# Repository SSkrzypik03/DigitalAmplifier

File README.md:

<p align="center">
  <picture>
    <source media="(prefers-color-scheme: dark)" srcset="img/volumia_logo_dark.png">
    <source media="(prefers-color-scheme: light)" srcset="img/volumia_logo_white.png">
    
  </picture>
</p>

<p align="center">
  High-performance Class-D audio amplifier with integrated DSP and PFFB
</p>

---

## Overview

Volumia is a high-performance stereo Class-D amplifier project based on the TPA3255 platform with Post-Filter Feedback (PFFB) and a dedicated STM32F446 DSP subsystem.

The goal is to deliver a compact and fully integrated 2×75 W amplifier combining digital signal processing, high audio quality and efficient power conversion.

## Main Features

## Audio & Electronics

- Class-D topology based on TPA3255
- Post-Filter Feedback (PFFB) architecture
- DSP processing using STM32F446
- 2×75 W RMS output power
- THD+N: TBD after laboratory measurements
- IMD: TBD after laboratory measurements

## Connectivity & User Interface

- USB Type-C input
- S/PDIF input
- RCA line input
- PREOUT output
- 3.83" OLED display
- IR remote control

## Mechanical Design

- Aluminum enclosure
- Glass front panel

---

# Hardware Overview

### Front View

### Rear View

### Internal View (Cover Removed)

## System Architecture

## Printed Circuit Boards

### Main Amplifier PCB

### Front Panel PCB

### Power Supply PCB

# Project Status

Current development progress:
- [x] First hardware iteration completed
- [ ] CAD model finalization
- [ ] Mechanical integration
- [ ] Firmware and DSP implementation
- [ ] Thermal validation
- [ ] EMC validation
- [ ] ESD robustness testing
- [ ] Full system testing

---

# Technologies Used

- KiCad
- STM32CubeIDE
- LTspice
- ARM Cortex-M4 Embedded C
- DSP simulation in Python
- Autodesk Fusion

---

# Repository Structure

```text
DigitalAmplifier/
├── hardware/
├── firmware/
├── spice/
└── README.md
```

---

# Support the Project

After building and validating a fully functional prototype, I plan to expand the project with an integrated audio streamer based on a Cortex-A35 processor running Linux or Android. This will enable music playback from services such as YouTube, Spotify, and TIDAL.

I would also like to further refine the industrial design, giving the amplifier a more modern and polished appearance.

The project is developed as Open Source from the very beginning, with a strong focus on quality, attention to detail, and long-term development.

If you would like to support my work and contribute to the project's future development, you can buy me a coffee:

☕ http://buycoffee.to/sskrzypik03

# Credits

Special thanks to [@vivadela](https://github.com/vivadela) for valuable support with the CAD design and mechanical development of the project.
---

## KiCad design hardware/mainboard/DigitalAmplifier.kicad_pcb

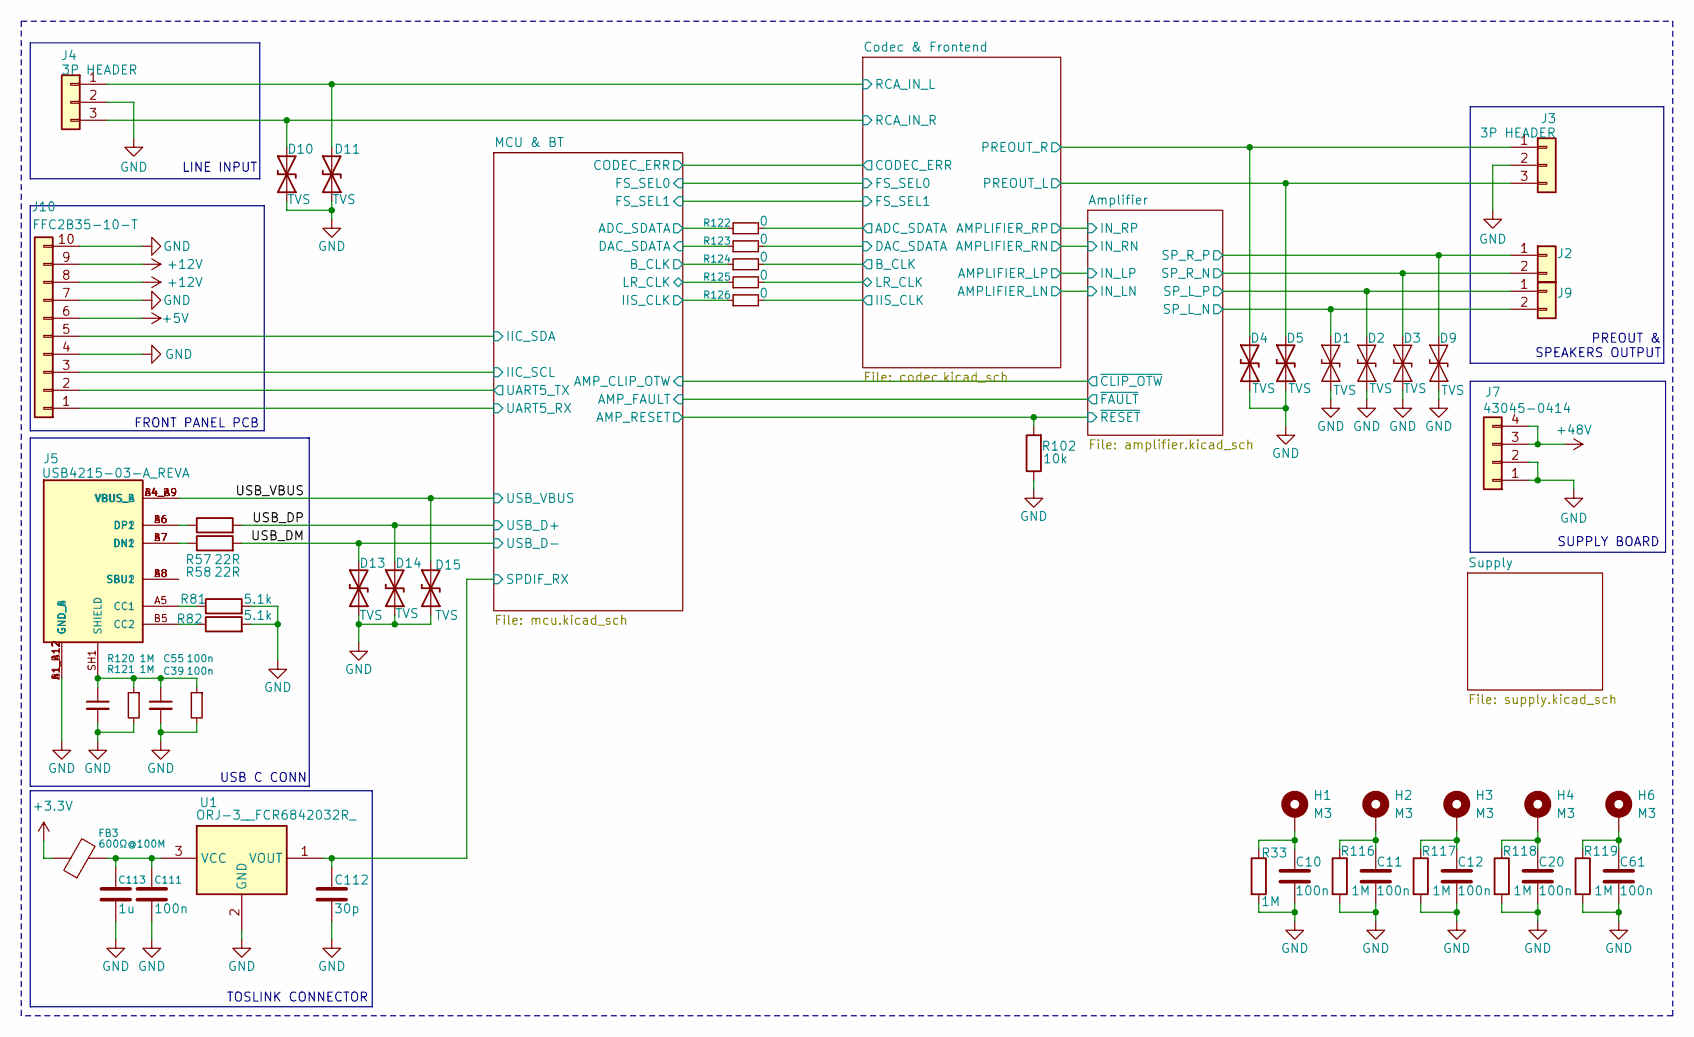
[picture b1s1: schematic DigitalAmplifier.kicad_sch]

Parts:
C10, C11, C12, C20, C39, C55, C61, C111: 100n; C_0603_1608Metric; Manufacturer_Part_Number 0603B104K500CT
C112: 30p; C_0603_1608Metric; Manufacturer_Part_Number C0603C300J5GACTU
C113: 1u; C_0603_1608Metric; Manufacturer_Part_Number CL10A105KB8NNNC
D1, D2, D3, D9: TVS; D_SMA; Manufacturer_Part_Number P4SMAJ6.5CA
D4, D5, D10, D11, D13, D14, D15: TVS; STN061050BL40; Manufacturer_Part_Number STN061050BL40-EA
FB3: 600Ω@100M; L_0603_1608Metric; Manufacturer_Part_Number BLM18AG601SN1D
H1, H2, H3, H4, H6: M3; WA-SMSI_97730256330; Manufacturer_Part_Number 9774040360R
J2, J9: Conn_01x02; 43650-02YY_151617; Manufacturer_Part_Number 43650-0215
J3, J4: 3P HEADER; JST_PH_B3B-PH-K_1x03_P2.00mm_Vertical; Manufacturer_Part_Number B3B-PH-K-S (LF)(SN)
J5: USB4215-03-A_REVA; GCT_USB4215-03-A_REVA; PARTREV A
J7: 43045-0414; 43045-04YY_121314; Manufacturer_Part_Number 43045-04YY_121314
J10: FFC2B35-10-T; FFC2B3510T; Manufacturer_Part_Number FFC2B3510T
R33, R116, R117, R118, R119, R120, R121: 1M; R_0603_1608Metric; Manufacturer_Part_Number RC0603JR-071ML
R57, R58: 22R; R_0603_1608Metric; Manufacturer_Part_Number WR06X220 JTL
R81, R82: 5.1k; R_0603_1608Metric; Manufacturer_Part_Number WR06X5101FTL
R102: 10k; R_0603_1608Metric; Manufacturer_Part_Number RC0603JR-0710KL
R122, R123, R124, R125, R126: 0; R_0402_1005Metric_Pad0.72x0.64mm_HandSolder; Manufacturer_Part_Number RC0402JR-070RL
U1: ORJ-3__FCR6842032R_; ORJ3FCR6842032R; Manufacturer_Part_Number ORJ-3 (FCR6842032R)

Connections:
+3.3V: FB3.1; also elsewhere on the board
+5V: J10.6; also elsewhere on the board
+12V: J10.8, J10.9; also elsewhere on the board
+48V: J7.3, J7.4; also elsewhere on the board
/Amplifier/SP_L_N: D1.2 (A2), J9.2; also elsewhere on the board
/Amplifier/SP_L_P: D2.2 (A2), J9.1; also elsewhere on the board
/Amplifier/SP_R_N: D3.2 (A2), J2.2; also elsewhere on the board
/Amplifier/SP_R_P: D9.2 (A2), J2.1; also elsewhere on the board
/Amplifier/~RESET: R102.2; also elsewhere on the board
/Codec & Frontend/ADC_SDATA: R122.2; also elsewhere on the board
/Codec & Frontend/B_CLK: R124.2; also elsewhere on the board
/Codec & Frontend/DAC_SDATA: R123.2; also elsewhere on the board
/Codec & Frontend/IIS_CLK: R126.2; also elsewhere on the board
/Codec & Frontend/LR_CLK: R125.2; also elsewhere on the board
/Codec & Frontend/PREOUT_L: D5.2 (A2), J3.3; also elsewhere on the board
/Codec & Frontend/PREOUT_R: D4.2 (A2), J3.1; also elsewhere on the board
/Codec & Frontend/RCA_IN_L: D11.2 (A2), J4.1; also elsewhere on the board
/Codec & Frontend/RCA_IN_R: D10.2 (A2), J4.3; also elsewhere on the board
/MCU & BT/ADC_SDATA: R122.1; also elsewhere on the board
/MCU & BT/B_CLK: R124.1; also elsewhere on the board
/MCU & BT/DAC_SDATA: R123.1; also elsewhere on the board
/MCU & BT/IIC_SCL: J10.3; also elsewhere on the board
/MCU & BT/IIC_SDA: J10.5; also elsewhere on the board
/MCU & BT/IIS_CLK: R126.1; also elsewhere on the board
/MCU & BT/LR_CLK: R125.1; also elsewhere on the board
/MCU & BT/SPDIF_RX: C112.1, U1.1 (VOUT); also elsewhere on the board
/MCU & BT/UART5_RX: J10.1; also elsewhere on the board
/MCU & BT/UART5_TX: J10.2; also elsewhere on the board
/USB_DM: D13.2 (A2), R58.2; also elsewhere on the board
/USB_DP: D14.2 (A2), R57.2; also elsewhere on the board
/USB_VBUS: D15.2 (A2), J5.A4_B9 (VBUS_A), J5.B4_A9 (VBUS_B); also elsewhere on the board
GND: C10.2, C11.2, C12.2, C20.2, C39.2, C55.2, C61.2, C111.2, C112.2, C113.2, D1.1 (A1), D2.1 (A1), D3.1 (A1), D4.1 (A1), D5.1 (A1), D9.1 (A1), D10.1 (A1), D11.1 (A1), D13.1 (A1), D14.1 (A1), D15.1 (A1), J3.2, J4.2, J5.A1_B12 (GND_A), J5.B1_A12 (GND_B), J7.1, J7.2, J10.4, J10.7, J10.10, R33.2, R81.2, R82.2, R102.1, R116.2, R117.2, R118.2, R119.2, R120.2, R121.2, U1.2 (GND); also elsewhere on the board
unnamed: C10.1, H1.1 (1_1), R33.1
unnamed: C11.1, H2.1 (1_1), R116.1
unnamed: C12.1, H3.1 (1_1), R117.1
unnamed: C20.1, H4.1 (1_1), R118.1
unnamed: C39.1, C55.1, J5.SH1 (SHIELD), J5.SH2 (SHIELD), J5.SH3 (SHIELD), J5.SH4 (SHIELD), R120.1, R121.1
unnamed: C61.1, H6.1 (1_1), R119.1
unnamed: J5.A5 (CC1), R81.1
unnamed: J5.B5 (CC2), R82.1
unnamed: J5.A7 (DN1), J5.B7 (DN2), R58.1
unnamed: J5.A6 (DP1), J5.B6 (DP2), R57.1
unnamed: J5.A8 (SBU1), J5.B8 (SBU2)
unnamed: C111.1, C113.1, FB3.2, U1.3 (VCC)

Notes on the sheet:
USB C CONN
SUPPLY BOARD
PREOUT & SPEAKERS OUTPUT
FRONT PANEL PCB
LINE INPUT
TOSLINK CONNECTOR

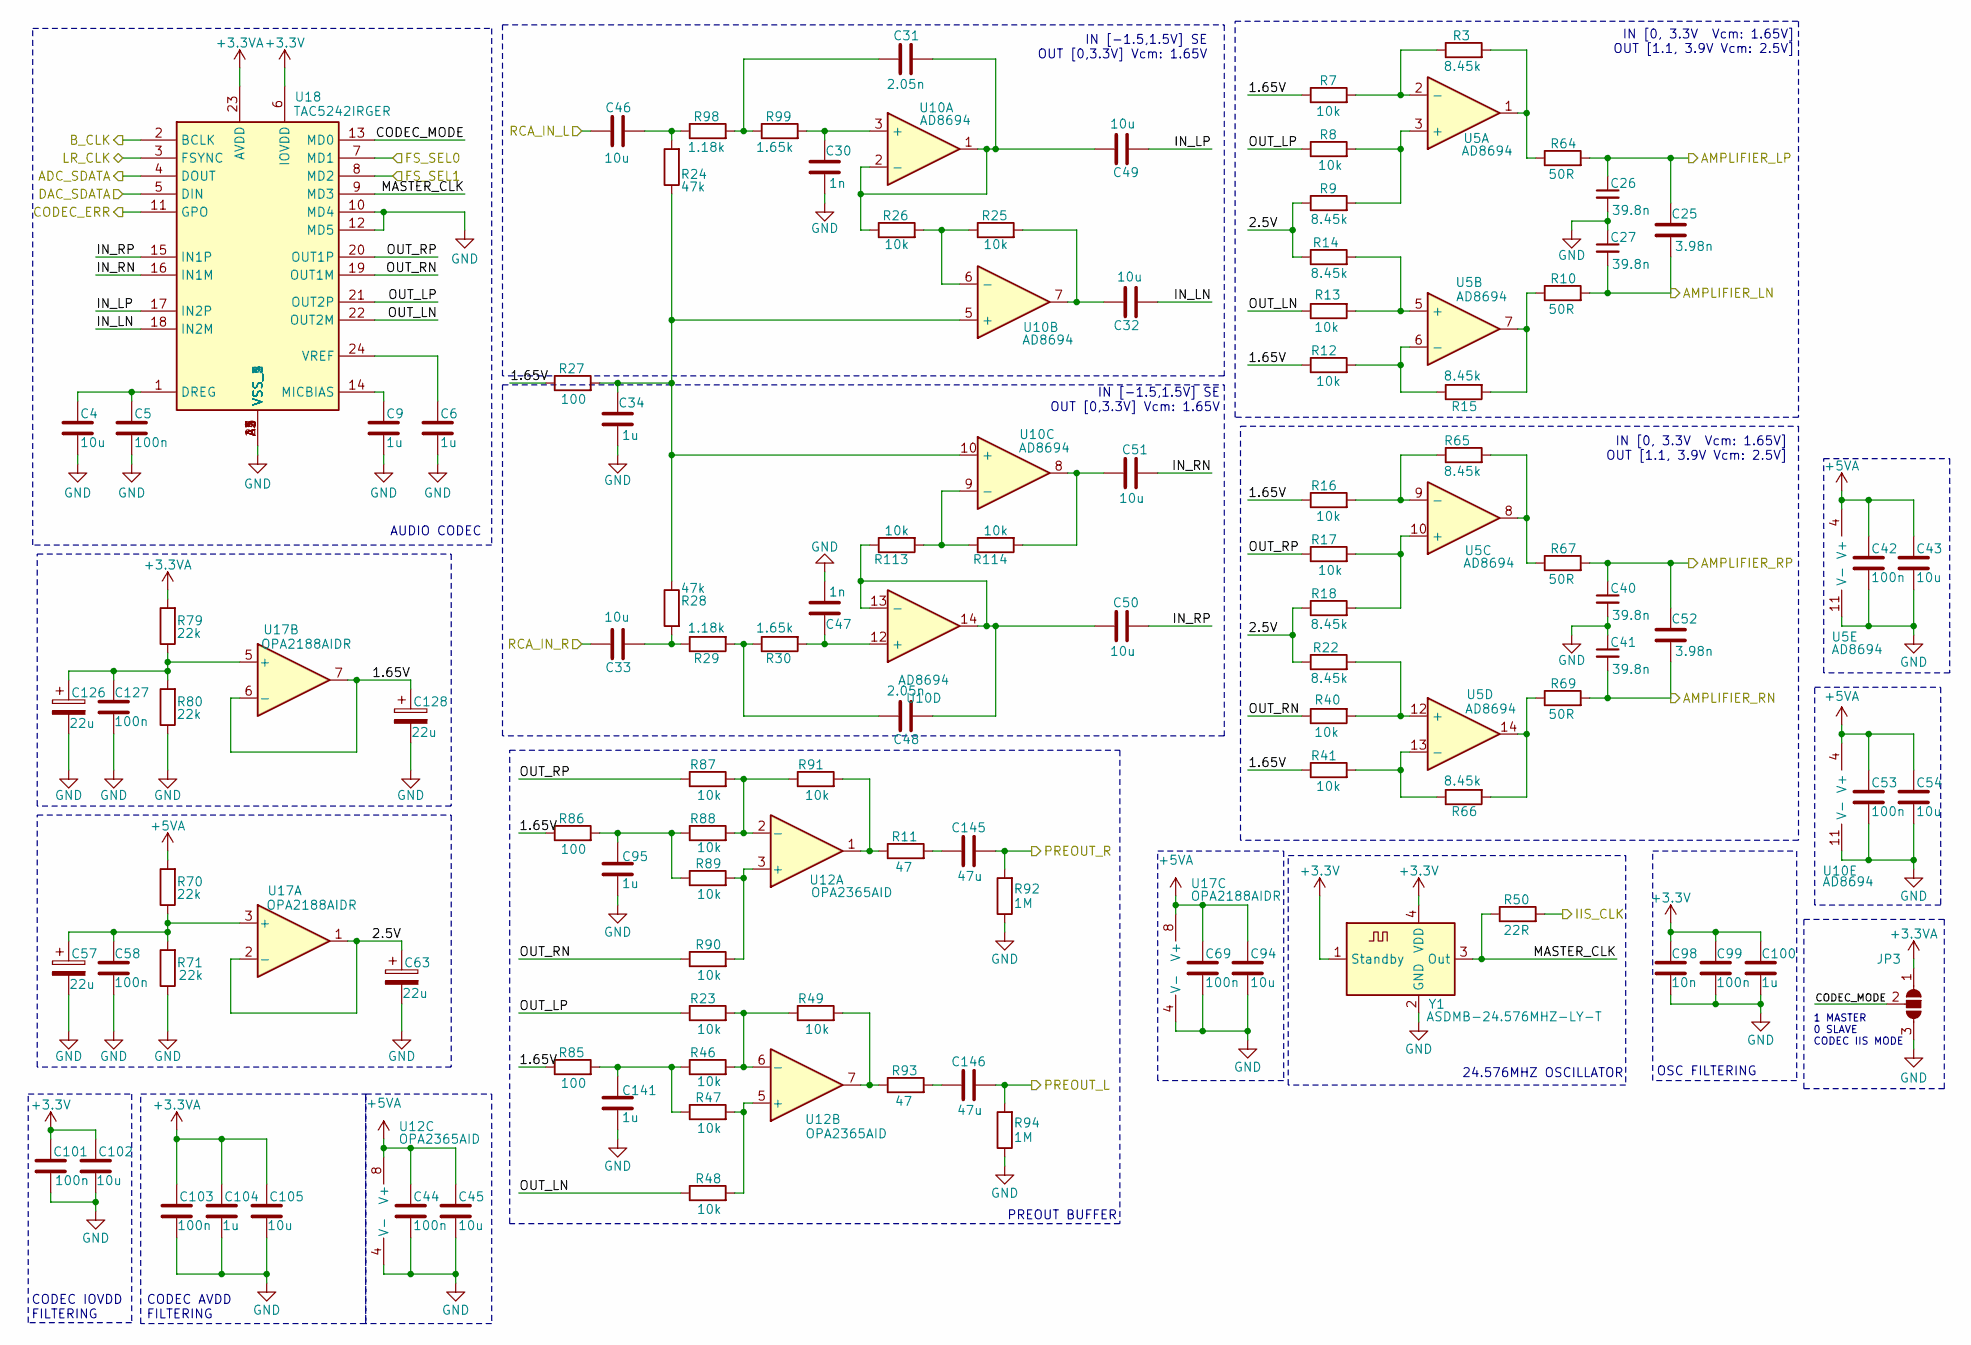
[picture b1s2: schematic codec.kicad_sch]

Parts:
C4, C43, C45, C54, C94, C102, C105: 10u; C_0603_1608Metric; Manufacturer_Part_Number GRM188R61E106KA73J
C5, C42, C44, C53, C58, C69, C99, C101, C103, C127: 100n; C_0603_1608Metric; Manufacturer_Part_Number 0603B104K500CT
C6, C9, C34, C100, C104: 1u; C_0603_1608Metric; Manufacturer_Part_Number CL10A105KB8NNNC
C25, C52: 3.98n; C_0603_1608Metric; Manufacturer_Part_Number GCM1885C1H392JA16D
C26, C27, C40, C41: 39.8n; C_0603_1608Metric; Manufacturer_Part_Number C0603C393K5RACTU
C30, C47: 1n; C_0603_1608Metric; Manufacturer_Part_Number 0603B102K500CT
C31, C48: 2.05n; C_0603_1608Metric; Manufacturer_Part_Number GCM188R71H272KA37D
C32, C33, C46, C49, C50, C51: 10u; C_0805_2012Metric; Manufacturer_Part_Number GRM21BR61E106KA73L
C57, C63, C126, C128: 22u; CAPPM3216X180N; Manufacturer_Part_Number 293D226X9010A2TE3
C95, C141: 1u; C_0805_2012Metric; Manufacturer_Part_Number CL21B105KAFNNNE
C98: 10n; C_0603_1608Metric; Manufacturer_Part_Number 06035C103KAT2A
C145, C146: 47u; C_0805_2012Metric; Manufacturer_Part_Number CL21A476MQYNNNE
JP3: SolderJumper_3_Open; SolderJumper-3_P1.3mm_Open_RoundedPad1.0x1.5mm
R3, R9, R14, R15, R18, R22, R65, R66: 8.45k; R_0603_1608Metric; Manufacturer_Part_Number ERA3AEB8661V
R7, R8, R12, R13, R16, R17, R23, R25, R26, R40, R41, R46, R47, R48, R49, R87, R88, R89, R90, R91, R113, R114: 10k; R_0603_1608Metric; Manufacturer_Part_Number RC0603JR-0710KL
R10, R64, R67, R69: 50R; R_0603_1608Metric; Manufacturer_Part_Number AR03BTCX0500
R11, R93: 47; R_0603_1608Metric; Manufacturer_Part_Number RC0603JR-0747RL
R24, R28: 47k; R_0603_1608Metric; Manufacturer_Part_Number RC0603JR-0747KL
R27, R85, R86: 100; R_0603_1608Metric; Manufacturer_Part_Number WR06X101 JTL
R29, R98: 1.18k; R_0603_1608Metric; Manufacturer_Part_Number ERA3AEB1181V
R30, R99: 1.65k; R_0603_1608Metric; Manufacturer_Part_Number ERA3AEB1651V
R50: 22R; R_0603_1608Metric; Manufacturer_Part_Number WR06X220 JTL
R70, R71, R79, R80: 22k; R_0603_1608Metric; Manufacturer_Part_Number WR06X2202FTL
R92, R94: 1M; R_0603_1608Metric; Manufacturer_Part_Number RC0603JR-071ML
U5, U10: AD8694; TSSOP-14_4.4x5mm_P0.65mm; Manufacturer_Part_Number AD8694
U12: OPA2365AID; SOIC-8_3.9x4.9mm_P1.27mm; Manufacturer_Part_Number OPA2365AID
U17: OPA2188AIDR; SOIC-8_3.9x4.9mm_P1.27mm; Manufacturer_Part_Number OPA2188AIDR
U18: TAC5242IRGER; Mouser Part Number 595-TAC5242IRGER
Y1: ASDMB-24.576MHZ-LY-T; Oscillator_SMD_Abracon_ASDMB-4Pin_2.5x2.0mm; Manufacturer_Part_Number ASDMB-24.576MHZ-LY-T

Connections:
+3.3V: C98.1, C99.1, C100.1, C101.1, C102.1, U18.6 (IOVDD), Y1.1 (Standby), Y1.4 (VDD); also elsewhere on the board
+3.3VA: C103.1, C104.1, C105.1, JP3.1 (A), R79.2, U18.23 (AVDD); also elsewhere on the board
+5VA: C42.1, C43.1, C44.1, C45.1, C53.1, C54.1, C69.1, C94.1, R70.2, U5.4 (V+), U10.4 (V+), U12.8 (V+), U17.8 (V+); also elsewhere on the board
/Amplifier/IN_LN: C25.2, C27.2, R10.2; also elsewhere on the board
/Amplifier/IN_LP: C25.1, C26.1, R64.2; also elsewhere on the board
/Amplifier/IN_RN: C41.2, C52.2, R69.2; also elsewhere on the board
/Amplifier/IN_RP: C40.1, C52.1, R67.2; also elsewhere on the board
/Codec & Frontend/1.65V: C128.1, R7.1, R12.1, R16.1, R27.1, R41.1, R85.1, R86.1, U17.6 (-), U17.7
/Codec & Frontend/2.5V: C63.1, R9.1, R14.1, R18.1, R22.1, U17.1, U17.2 (-)
/Codec & Frontend/ADC_SDATA: U18.4 (DOUT); also elsewhere on the board
/Codec & Frontend/B_CLK: U18.2 (BCLK); also elsewhere on the board
/Codec & Frontend/CODEC_ERR: U18.11 (GPO); also elsewhere on the board
/Codec & Frontend/CODEC_MODE: JP3.2 (C), U18.13 (MD0)
/Codec & Frontend/DAC_SDATA: U18.5 (DIN); also elsewhere on the board
/Codec & Frontend/FS_SEL0: U18.7 (MD1); also elsewhere on the board
/Codec & Frontend/FS_SEL1: U18.8 (MD2); also elsewhere on the board
/Codec & Frontend/IIS_CLK: R50.2; also elsewhere on the board
/Codec & Frontend/IN_LN: C32.1, U18.18 (IN2M)
/Codec & Frontend/IN_LP: C49.2, U18.17 (IN2P)
/Codec & Frontend/IN_RN: C51.2, U18.16 (IN1M)
/Codec & Frontend/IN_RP: C50.2, U18.15 (IN1P)
/Codec & Frontend/LR_CLK: U18.3 (FSYNC); also elsewhere on the board
/Codec & Frontend/MASTER_CLK: R50.1, U18.9 (MD3), Y1.3 (Out)
/Codec & Frontend/OUT_LN: R13.1, R48.1, U18.22 (OUT2M)
/Codec & Frontend/OUT_LP: R8.1, R23.1, U18.21 (OUT2P)
/Codec & Frontend/OUT_RN: R40.1, R90.1, U18.19 (OUT1M)
/Codec & Frontend/OUT_RP: R17.1, R87.1, U18.20 (OUT1P)
/Codec & Frontend/PREOUT_L: C146.2, R94.2; also elsewhere on the board
/Codec & Frontend/PREOUT_R: C145.2, R92.2; also elsewhere on the board
/Codec & Frontend/RCA_IN_L: C46.1; also elsewhere on the board
/Codec & Frontend/RCA_IN_R: C33.1; also elsewhere on the board
GND: C4.2, C5.2, C6.2, C9.2, C26.2, C27.1, C30.2, C34.2, C40.2, C41.1, C42.2, C43.2, C44.2, C45.2, C47.2, C53.2, C54.2, C57.2, C58.2, C63.2, C69.2, C94.2, C95.2, C98.2, C99.2, C100.2, C101.2, C102.2, C103.2, C104.2, C105.2, C126.2, C127.2, C128.2, C141.2, JP3.3 (B), R71.1, R80.1, R92.1, R94.1, U5.11 (V-), U10.11 (V-), U12.4 (V-), U17.4 (V-), U18.10 (MD4), U18.12 (MD5), U18.25 (VSS_1), U18.A1 (VSS_2), U18.A2 (VSS_3), U18.A3 (VSS_4), U18.A4 (VSS_5), Y1.2 (GND); also elsewhere on the board
unnamed: C31.1, R98.2, R99.1
unnamed: C32.2, R25.2, U10.7
unnamed: C33.2, R28.2, R29.1
unnamed: C46.2, R24.2, R98.1
unnamed: C48.1, R29.2, R30.1
unnamed: C51.1, R114.2, U10.8
unnamed: C95.1, R86.2, R88.1, R89.1
unnamed: C141.1, R46.1, R47.1, R85.2
unnamed: C145.1, R11.2
unnamed: C146.1, R93.2
unnamed: R3.2, R64.1, U5.1
unnamed: R10.1, R15.2, U5.7
unnamed: R11.1, R91.2, U12.1
unnamed: R49.2, R93.1, U12.7
unnamed: R65.2, R67.1, U5.8
unnamed: R66.2, R69.1, U5.14
unnamed: R8.2, R9.2, U5.3 (+)
unnamed: R3.1, R7.2, U5.2 (-)
unnamed: R13.2, R14.2, U5.5 (+)
unnamed: R12.2, R15.1, U5.6 (-)
unnamed: R17.2, R18.2, U5.10 (+)
unnamed: R16.2, R65.1, U5.9 (-)
unnamed: R22.2, R40.2, U5.12 (+)
unnamed: R41.2, R66.1, U5.13 (-)
unnamed: C30.1, R99.2, U10.3 (+)
unnamed: C31.2, C49.1, R26.1, U10.1, U10.2 (-)
unnamed: C34.1, R24.1, R27.2, R28.1, U10.5 (+), U10.10 (+)
unnamed: R25.1, R26.2, U10.6 (-)
unnamed: R113.2, R114.1, U10.9 (-)
unnamed: C47.1, R30.2, U10.12 (+)
unnamed: C48.2, C50.1, R113.1, U10.13 (-), U10.14
unnamed: R89.2, R90.2, U12.3 (+)
unnamed: R87.2, R88.2, R91.1, U12.2 (-)
unnamed: R47.2, R48.2, U12.5 (+)
unnamed: R23.2, R46.2, R49.1, U12.6 (-)
unnamed: C57.1, C58.1, R70.1, R71.2, U17.3 (+)
unnamed: C126.1, C127.1, R79.1, R80.2, U17.5 (+)
unnamed: C4.1, C5.1, U18.1 (DREG)
unnamed: C9.1, U18.14 (MICBIAS)
unnamed: C6.1, U18.24 (VREF)

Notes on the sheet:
CODEC AVDD FILTERING
IN [0, 3.3V Vcm: 1.65V] OUT [1.1, 3.9V Vcm: 2.5V]
PREOUT BUFFER
OSC FILTERING
IN [-1.5,1.5V] SE OUT [0,3.3V] Vcm: 1.65V
1 MASTER 0 SLAVE CODEC IIS MODE
AUDIO CODEC
24.576MHZ OSCILLATOR
CODEC IOVDD FILTERING

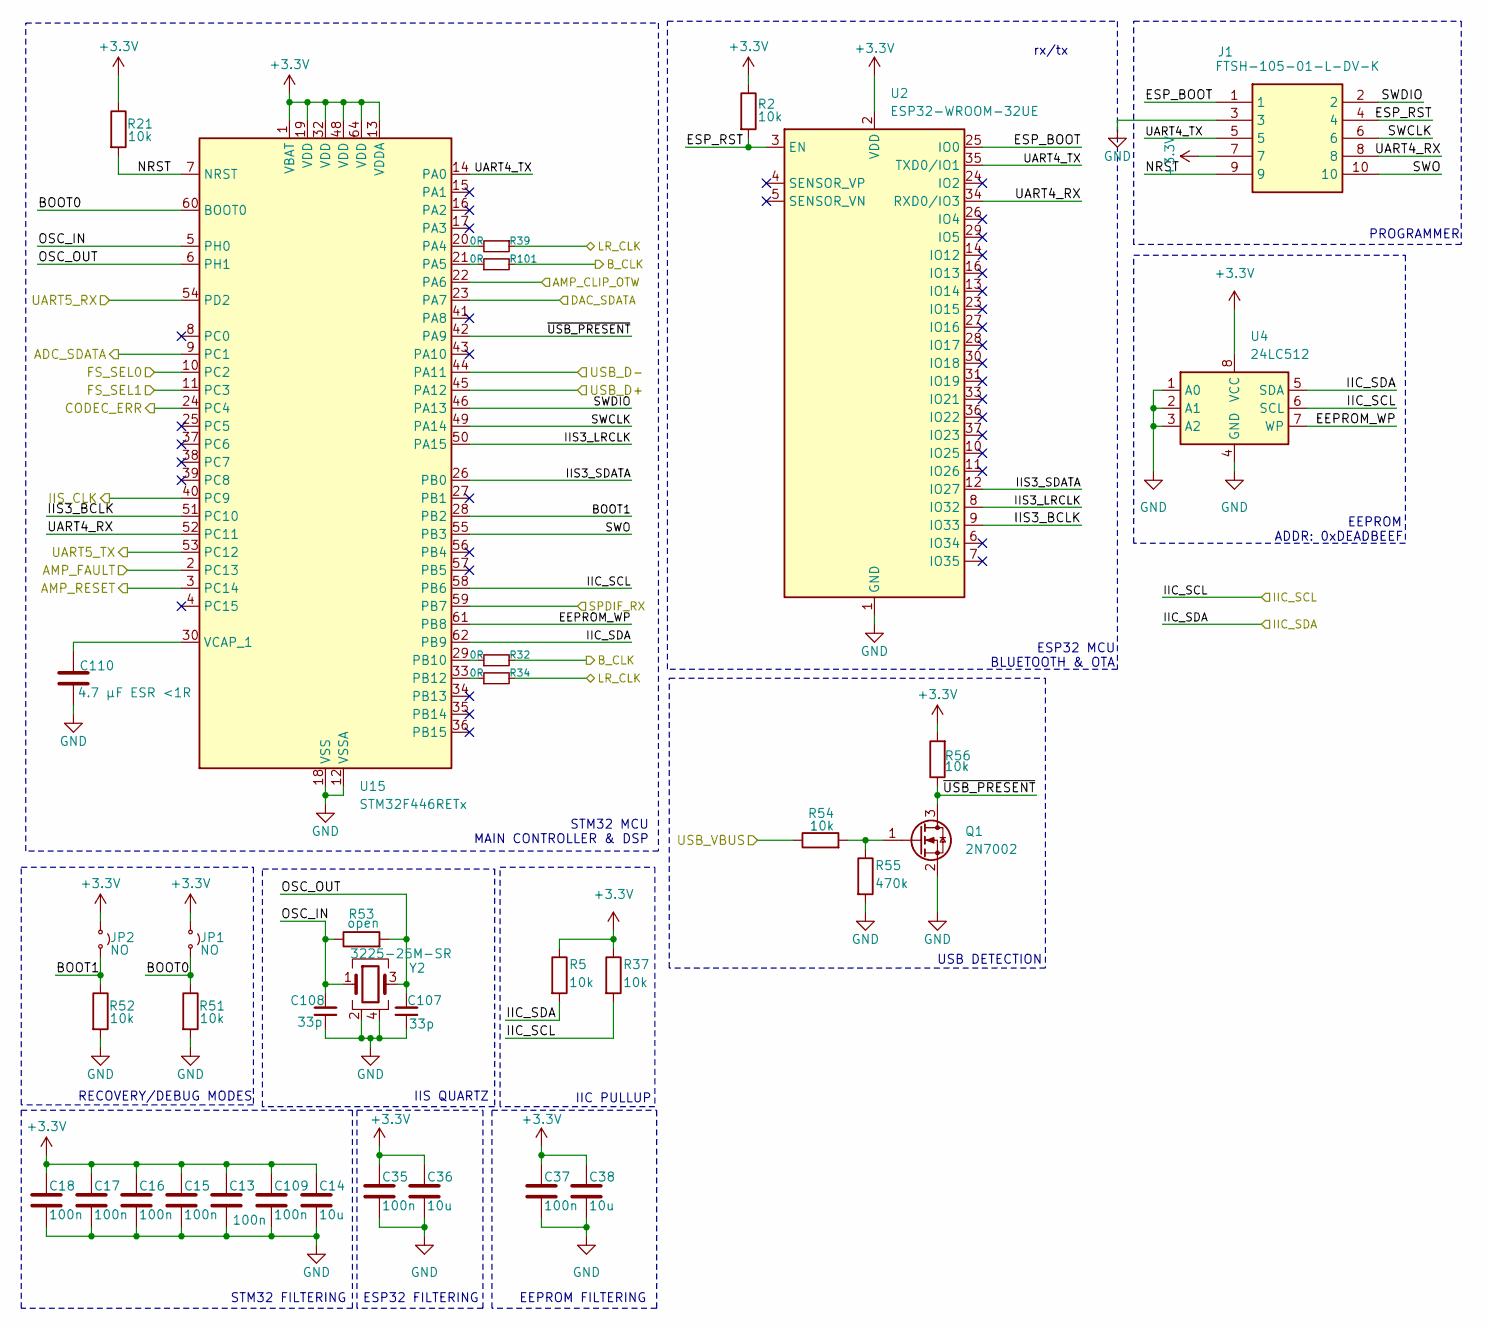
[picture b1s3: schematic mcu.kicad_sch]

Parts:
C13, C15, C16, C17, C18, C35, C37, C109: 100n; C_0603_1608Metric; Manufacturer_Part_Number 0603B104K500CT
C14, C36, C38: 10u; C_0603_1608Metric; Manufacturer_Part_Number GRM188R61E106KA73J
C107, C108: 33p; C_0603_1608Metric; Manufacturer_Part_Number CC0603JRNPO9BN330
C110: 4.7 μF ESR <1R; C_0603_1608Metric; Manufacturer_Part_Number CL10A475KP8NNNC
J1: FTSH-105-01-L-DV-K; FTSH10501LDVK; Manufacturer_Part_Number FTSH-105-01-L-DV-K
JP1, JP2: NO; PinHeader_2x01_P1.27mm_Vertical; Manufacturer_Part_Number DS1031-01-1*2P8BV3-1
Q1: 2N7002; SOT-23; Manufacturer_Part_Number 2N7002-G
R2, R5, R21, R37, R51, R52, R54, R56: 10k; R_0603_1608Metric; Manufacturer_Part_Number RC0603JR-0710KL
R32, R34, R39, R101: 0R; R_0603_1608Metric; Manufacturer_Part_Number RC0603JR-070RL
R53: open; R_0603_1608Metric
R55: 470k; R_0603_1608Metric; Manufacturer_Part_Number RC0603FR-07470KL
U2: ESP32-WROOM-32UE; Manufacturer_Part_Number ESP32-WROOM-32UE
U4: 24LC512; SOIC-8_3.9x4.9mm_P1.27mm; Manufacturer_Part_Number 24LC512-I/SN
U15: STM32F446RETx; LQFP-64_10x10mm_P0.5mm; Manufacturer_Part_Number STM32F446RETx
Y2: 3225-25M-SR; 322525MSR; Manufacturer_Part_Number 3225-25M-SR

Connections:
+3.3V: C13.1, C14.1, C15.1, C16.1, C17.1, C18.1, C35.1, C36.1, C37.1, C38.1, C109.1, J1.7, JP1.1 (A), JP2.1 (A), R2.1, R5.1, R21.1, R37.1, R56.2, U2.2 (VDD), U4.8 (VCC), U15.1 (VBAT), U15.13 (VDDA), U15.19 (VDD), U15.32 (VDD), U15.48 (VDD), U15.64 (VDD); also elsewhere on the board
/Amplifier/~CLIP_OTW: U15.22 (PA6); also elsewhere on the board
/Amplifier/~FAULT: U15.2 (PC13); also elsewhere on the board
/Amplifier/~RESET: U15.3 (PC14); also elsewhere on the board
/Codec & Frontend/CODEC_ERR: U15.24 (PC4); also elsewhere on the board
/Codec & Frontend/FS_SEL0: U15.10 (PC2); also elsewhere on the board
/Codec & Frontend/FS_SEL1: U15.11 (PC3); also elsewhere on the board
/MCU & BT/ADC_SDATA: U15.9 (PC1); also elsewhere on the board
/MCU & BT/BOOT0: JP1.2 (B), R51.1, U15.60 (BOOT0)
/MCU & BT/BOOT1: JP2.2 (B), R52.1, U15.28 (PB2)
/MCU & BT/B_CLK: R32.2, R101.2; also elsewhere on the board
/MCU & BT/DAC_SDATA: U15.23 (PA7); also elsewhere on the board
/MCU & BT/EEPROM_WP: U4.7 (WP), U15.61 (PB8)
/MCU & BT/ESP_BOOT: J1.1, U2.25 (IO0)
/MCU & BT/ESP_RST: J1.4, R2.2, U2.3 (EN)
/MCU & BT/IIC_SCL: R37.2, U4.6 (SCL), U15.58 (PB6); also elsewhere on the board
/MCU & BT/IIC_SDA: R5.2, U4.5 (SDA), U15.62 (PB9); also elsewhere on the board
/MCU & BT/IIS3_BCLK: U2.9 (IO33), U15.51 (PC10)
/MCU & BT/IIS3_LRCLK: U2.8 (IO32), U15.50 (PA15)
/MCU & BT/IIS3_SDATA: U2.12 (IO27), U15.26 (PB0)
/MCU & BT/IIS_CLK: U15.40 (PC9); also elsewhere on the board
/MCU & BT/LR_CLK: R34.2, R39.1; also elsewhere on the board
/MCU & BT/NRST: J1.9, R21.2, U15.7 (NRST)
/MCU & BT/OSC_IN: C108.2, R53.1, U15.5 (PH0), Y2.1
/MCU & BT/OSC_OUT: C107.2, R53.2, U15.6 (PH1), Y2.3
/MCU & BT/SPDIF_RX: U15.59 (PB7); also elsewhere on the board
/MCU & BT/SWCLK: J1.6, U15.49 (PA14)
/MCU & BT/SWDIO: J1.2, U15.46 (PA13)
/MCU & BT/SWO: J1.10, U15.55 (PB3)
/MCU & BT/UART4_RX: J1.8, U2.34 (RXD0/IO3), U15.52 (PC11)
/MCU & BT/UART4_TX: J1.5, U2.35 (TXD0/IO1), U15.14 (PA0)
/MCU & BT/UART5_RX: U15.54 (PD2); also elsewhere on the board
/MCU & BT/UART5_TX: U15.53 (PC12); also elsewhere on the board
/MCU & BT/~USB_PRESENT: Q1.3 (D), R56.1, U15.42 (PA9)
/USB_DM: U15.44 (PA11); also elsewhere on the board
/USB_DP: U15.45 (PA12); also elsewhere on the board
/USB_VBUS: R54.1; also elsewhere on the board
GND: C13.2, C14.2, C15.2, C16.2, C17.2, C18.2, C35.2, C36.2, C37.2, C38.2, C107.1, C108.1, C109.2, C110.2, J1.3, Q1.2 (S), R51.2, R52.2, R55.2, U2.1 (GND), U2.15 (GND), U2.38 (GND), U2.39 (GND), U4.1 (A0), U4.2 (A1), U4.3 (A2), U4.4 (GND), U15.12 (VSSA), U15.18 (VSS), U15.31 (VSS), U15.47 (VSS), U15.63 (VSS), Y2.2, Y2.4; also elsewhere on the board
unnamed: Q1.1 (G), R54.2, R55.1
unnamed: R39.2, U15.20 (PA4)
unnamed: R101.1, U15.21 (PA5)
unnamed: R32.1, U15.29 (PB10)
unnamed: R34.1, U15.33 (PB12)
unnamed: C110.1, U15.30 (VCAP_1)

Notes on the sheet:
EEPROM
ESP32 MCU
rx/tx
IIS QUARTZ
RECOVERY/DEBUG MODES
ADDR: 0xDEADBEEF
STM32 FILTERING
PROGRAMMER
BLUETOOTH & OTA
EEPROM FILTERING
IIC PULLUP
STM32 MCU MAIN CONTROLLER & DSP
USB DETECTION
ESP32 FILTERING

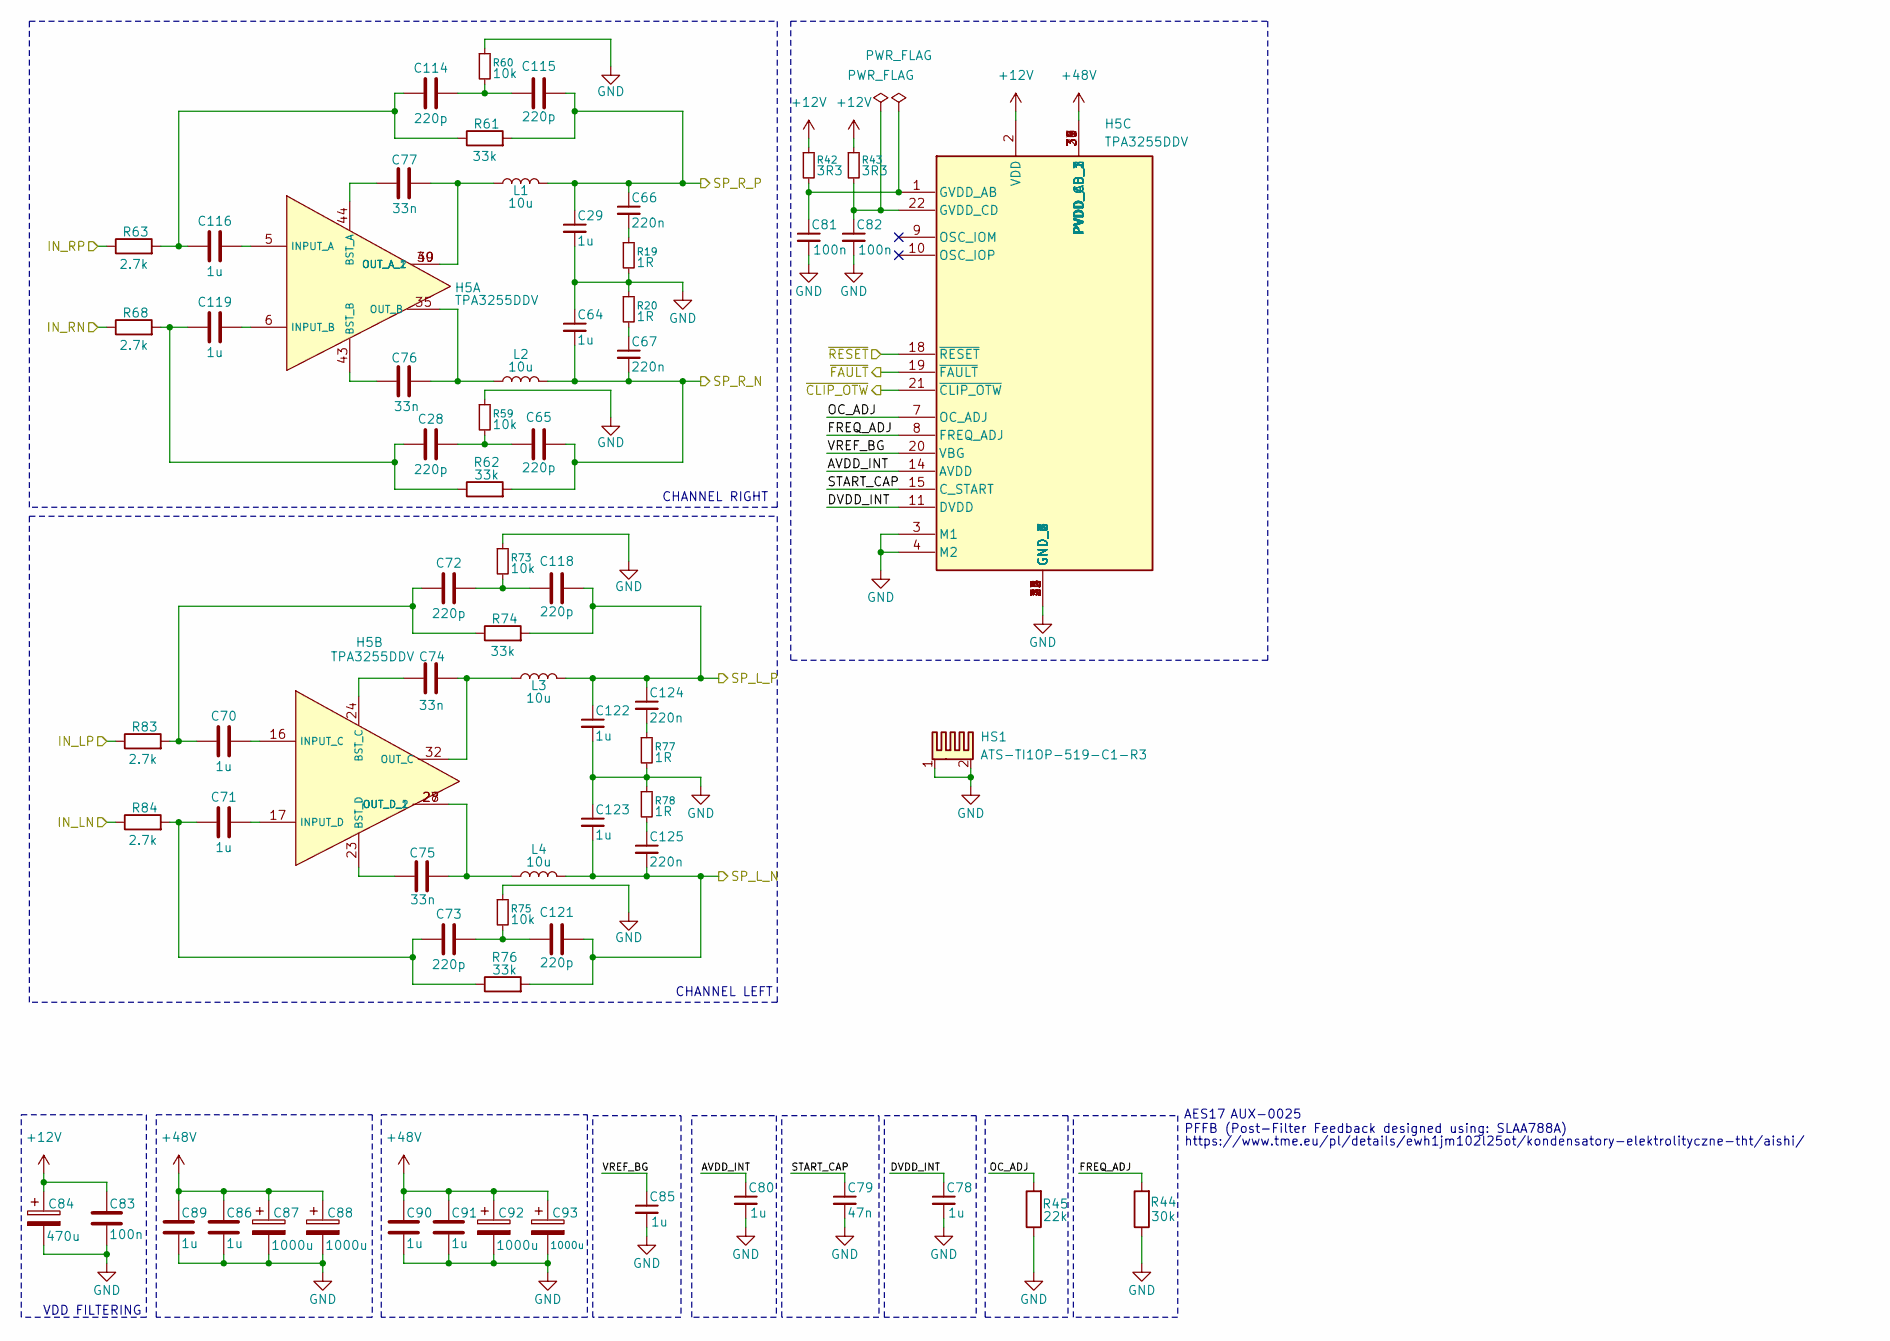
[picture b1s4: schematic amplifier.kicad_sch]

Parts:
C28, C65, C72, C73, C114, C115, C118, C121: 220p; C_1206_3216Metric; Manufacturer_Part_Number CC1206JRNPOBBN221
C29, C64, C122, C123: 1u; PHE-BV_KEM; Manufacturer_Part_Number PHE426HB7100JR06
C66, C67, C124, C125: 220n; C_1206_3216Metric; Manufacturer_Part_Number CL21B224KBFNNNG
C70, C71, C116, C119: 1u; C_0805_2012Metric; Manufacturer_Part_Number CL21B105KAFNNNE
C74, C75, C76, C77: 33n; C_1206_3216Metric; Manufacturer_Part_Number 1206B333K101CT
C78, C80, C85, C86, C89, C90, C91: 1u; C_0603_1608Metric; Manufacturer_Part_Number CL10A105KB8NNNC
C79: 47n; C_0603_1608Metric; Manufacturer_Part_Number CC0603KRX7R9BB473
C81, C82, C83: 100n; C_0603_1608Metric; Manufacturer_Part_Number 0603B104K500CT
C84: 470u; CP_EIA-6032-20_AVX-F; Manufacturer_Part_Number TAJC107K016RNJ
C87, C88, C92, C93: 1000u; CAPPRD750W80D1600H2500; Manufacturer_Part_Number EWH1JM102L25OT
H5: TPA3255DDV; SOP64P810X120-44N; Mouser Part Number 595-TPA3255DDV
HS1: ATS-TI1OP-519-C1-R3; Manufacturer_Part_Number ATS-TI1OP-519-C1-R3
L1, L2, L3, L4: 10u; MA5172AE; Manufacturer_Part_Number MA5172-AE
R19, R20, R77, R78: 1R; R_0805_2012Metric; Manufacturer_Part_Number RC0805FR-071RL
R42, R43: 3R3; R_0603_1608Metric; Manufacturer_Part_Number AC0603FR-073R3L
R44: 30k; R_0603_1608Metric; Manufacturer_Part_Number ERJPA3F3002V
R45: 22k; R_0603_1608Metric; Manufacturer_Part_Number WR06X2202FTL
R59, R60, R73, R75: 10k; R_0805_2012Metric; Manufacturer_Part_Number RC0805FR-0710KL
R61, R62, R74, R76: 33k; R_0805_2012Metric; Manufacturer_Part_Number RC0805FR-0733KL
R63, R68, R83, R84: 2.7k; R_0603_1608Metric; Manufacturer_Part_Number WR06X2701FTL

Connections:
+12V: C83.1, C84.1, H5.2 (VDD), R42.1, R43.1; also elsewhere on the board
+48V: C86.1, C87.1, C88.1, C89.1, C90.1, C91.1, C92.1, C93.1, H5.29 (PVDD_CD_1), H5.30 (PVDD_CD_2), H5.31 (PVDD_CD_3), H5.36 (PVDD_AB_1), H5.37 (PVDD_AB_2), H5.38 (PVDD_AB_3); also elsewhere on the board
/Amplifier/AVDD_INT: C80.1, H5.14 (AVDD)
/Amplifier/DVDD_INT: C78.1, H5.11 (DVDD)
/Amplifier/FREQ_ADJ: H5.8 (FREQ_ADJ), R44.2
/Amplifier/IN_LN: R84.1; also elsewhere on the board
/Amplifier/IN_LP: R83.1; also elsewhere on the board
/Amplifier/IN_RN: R68.1; also elsewhere on the board
/Amplifier/IN_RP: R63.1; also elsewhere on the board
/Amplifier/OC_ADJ: H5.7 (OC_ADJ), R45.2
/Amplifier/SP_L_N: C121.1, C123.2, C125.2, L4.2, R76.2; also elsewhere on the board
/Amplifier/SP_L_P: C118.1, C122.1, C124.1, L3.2, R74.2; also elsewhere on the board
/Amplifier/SP_R_N: C64.2, C65.1, C67.2, L2.2, R62.2; also elsewhere on the board
/Amplifier/SP_R_P: C29.1, C66.1, C115.1, L1.2, R61.2; also elsewhere on the board
/Amplifier/START_CAP: C79.1, H5.15 (C_START)
/Amplifier/VREF_BG: C85.1, H5.20 (VBG)
/Amplifier/~CLIP_OTW: H5.21 (~CLIP_OTW); also elsewhere on the board
/Amplifier/~FAULT: H5.19 (~FAULT); also elsewhere on the board
/Amplifier/~RESET: H5.18 (~RESET); also elsewhere on the board
GND: C29.2, C64.1, C78.2, C79.2, C80.2, C81.2, C82.2, C83.2, C84.2, C85.2, C86.2, C87.2, C88.2, C89.2, C90.2, C91.2, C92.2, C93.2, C122.2, C123.1, H5.3 (M1), H5.4 (M2), H5.12 (GND_1), H5.13 (GND_2), H5.25 (GND_3), H5.26 (GND_4), H5.33 (GND_5), H5.34 (GND_6), H5.41 (GND_7), H5.42 (GND_8), HS1.1, HS1.2, R19.2, R20.1, R44.1, R45.1, R59.1, R60.1, R73.1, R75.1, R77.2, R78.1; also elsewhere on the board
unnamed: C28.1, C65.2, R59.2
unnamed: C66.2, R19.1
unnamed: C67.1, R20.2
unnamed: C70.1, C72.2, R74.1, R83.2
unnamed: C71.1, C73.2, R76.1, R84.2
unnamed: C114.1, C115.2, R60.2
unnamed: C114.2, C116.1, R61.1, R63.2
unnamed: C72.1, C118.2, R73.2
unnamed: C28.2, C119.1, R62.1, R68.2
unnamed: C73.1, C121.2, R75.2
unnamed: C124.2, R77.1
unnamed: C125.1, R78.2
unnamed: C77.1, H5.44 (BST_A)
unnamed: C76.1, H5.43 (BST_B)
unnamed: C116.2, H5.5 (INPUT_A)
unnamed: C119.2, H5.6 (INPUT_B)
unnamed: C77.2, H5.39 (OUT_A_1), H5.40 (OUT_A_2), L1.1
unnamed: C76.2, H5.35 (OUT_B), L2.1
unnamed: C74.2, H5.24 (BST_C)
unnamed: C75.1, H5.23 (BST_D)
unnamed: C70.2, H5.16 (INPUT_C)
unnamed: C71.2, H5.17 (INPUT_D)
unnamed: C74.1, H5.32 (OUT_C), L3.1
unnamed: C75.2, H5.27 (OUT_D_1), H5.28 (OUT_D_2), L4.1
unnamed: C81.1, H5.1 (GVDD_AB), R42.2
unnamed: C82.1, H5.22 (GVDD_CD), R43.2

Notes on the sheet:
CHANNEL LEFT
CHANNEL RIGHT
VDD FILTERING
PFFB (Post-Filter Feedback designed using: SLAA788A)
AES17
https://www.tme.eu/pl/details/ewh1jm102l25ot/kondensatory-elektrolityczne-tht/aishi/
AUX-0025
